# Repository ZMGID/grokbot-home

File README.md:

# grokbot-home

我的 Grok Bot「家」：换到新的 Grok Bot 账号时，让新号上的 bot 按这个仓库把自己和其他所有 bot 一起配好，做到基本无缝切换。

## 怎么用

仓库是**公开**的（2026-10-08 起），新号上的 bot 不用登录 GitHub 就能匿名克隆、读 `BOOTSTRAP.md`。Composio API key 只以**加密**形式放在 `secrets/*.enc`，解密口令只有我知道（应用连接只走 `composio-pg`，不装官方 GitHub/Origin 等连接器）。

在新号上打开任意一个 Grok Bot（一般是默认的主 bot），对它说：

```text
按这个仓库配置自己：https://github.com/ZMGID/grokbot-home
```

它会读 [`BOOTSTRAP.md`](BOOTSTRAP.md)，然后依次：

1. （Step 0）匿名克隆本仓库 → 用密码框（secret-request）向我要口令 `GROKBOT_HOME_PASSPHRASE` → 解密 `secrets/COMPOSIO_API_KEY.enc` 到 `~/.composio_pg_key`（连不上就换 `.box-current.enc`）→ 从 `connectors/composio-pg/` 装好并添加 composio-pg；
2. （Step 1）用 Composio 里 GitHub（ZMGID）的 token 登录 `gh`——只有往仓库推送（写回、每日同步）才需要；
3. 跑 `setup.sh` 装好工具环境（KiCad、PlatformIO、cadquery、Composio SDK 等）；
4. 确认 `composio-pg` 已接通；pstack 插件可选（原为 dr eggbot 安装）；导入 `skills/` 里的技能（若有）；
5. 按 `bots/grok-bot/` 设置自己为 **小萌**（主 bot；原名 Grok Bot）并读 `CONTEXT.md`；
6. 用 CreateAgent 把 `bots/` 下其他每个 bot（小枳、仓库管家、代码工程师、搭建运维、事务秘书、硬件工程师……，以 `bots/index.json` 为准）重新建出来，并重建它们的定时任务；
7. 自检，最后把新学到的东西写回仓库。

我需要亲自做的只有：在密码框里填一次仓库口令（解密失败时才要 Composio key 本身；`gh` 设备码只在推送权限拿不到时备用）。

## 目录

| 路径 | 内容 |
|---|---|
| `BOOTSTRAP.md` | 写给新 bot 的开机步骤（英文为主，附中文） |
| `CONTEXT.md` | 关于我的共享记忆：习惯、账号、项目进度、换号决定 |
| `bots/<名字>/` | 每个 bot 一个文件夹：`profile.md`（设定）、`CONTEXT.md`（它自己的记忆）、`routines.md`（定时任务） |
| `connectors/` | 连接器清单 + `composio-pg` 启动脚本（不含密钥） |
| `skills/` | 用户自建技能（目前有 `tiktok`：TikTok巴西站竞品调研） |
| `setup.sh` | 工具环境安装脚本（可重复运行） |
| `scripts/` | 每日同步任务说明和脚本、密钥扫描 `secret-scan.sh`、加解密 `secret-crypt.py` |
| `secrets/` | 只放加密后的密钥（`*.enc`），见 `secrets/README.md` |
| `projects/` | 项目文件（仿 TourBox 创作控制器） |

## 规矩

- **仓库是公开的，明文密钥永远不进仓库**。唯一例外是 `secrets/*.enc`：用 `scripts/secret-crypt.py` 加密后的 Composio key。口令只通过 bot 的密码框（secret prompt）给，绝不写进仓库或聊天。推送前必须 `bash scripts/secret-scan.sh` 通过。
- 每个号用完，新记住的东西写回对应的 `CONTEXT.md` 再推送。仓库管家每天凌晨 3:14（北京时间）自动同步一次。
- 仓库公开后，里面的共享记忆（`CONTEXT.md`、`bots/*/CONTEXT.md`、`bots/*/raw/memory/`）任何人都能看到；不要再写进不想公开的内容。不做 export-bot-template 分享模板。

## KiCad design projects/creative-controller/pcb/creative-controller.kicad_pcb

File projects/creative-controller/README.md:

# CreativeDial delivery package (Rev A1, 2026-10-08)
中文完整说明见 docs/README.md；设计审查报告（问题清单、修复、料号核验表、上电调试清单）见 **docs/审查报告.md**。

- Mechanical: mechanical/ (print-ready STL in print/)
- PCB (KiCad 9): pcb/ — regenerate with `cd pcb && ./route.sh && ./export.sh`; JLCPCB outputs in pcb/fab/
  (gerbers zip, BOM_JLCPCB.csv, CPL_JLCPCB.csv, BOM_detailed.csv with LCSC stock/price/Basic-Extended/links, ERC/DRC reports)
- Firmware: firmware/ (PlatformIO, Arduino-ESP32); prebuilt merged image firmware/bin/creativedial-esp32s3-merged.bin @0x0.
  Hardware self-test: hold TOP key while plugging in USB (or send `{"cmd":"selftest","on":true}`), watch serial at 115200.
- Config app: software/

Status: ERC 0 errors / DRC 0 errors (silkscreen warnings only), firmware builds cleanly. Not yet prototyped — see docs/审查报告.md §6 for remaining risks
(ENC2 mouse-encoder footprint is a placeholder; confirm CPL rotations in JLC preview; battery must have its own protection PCM).

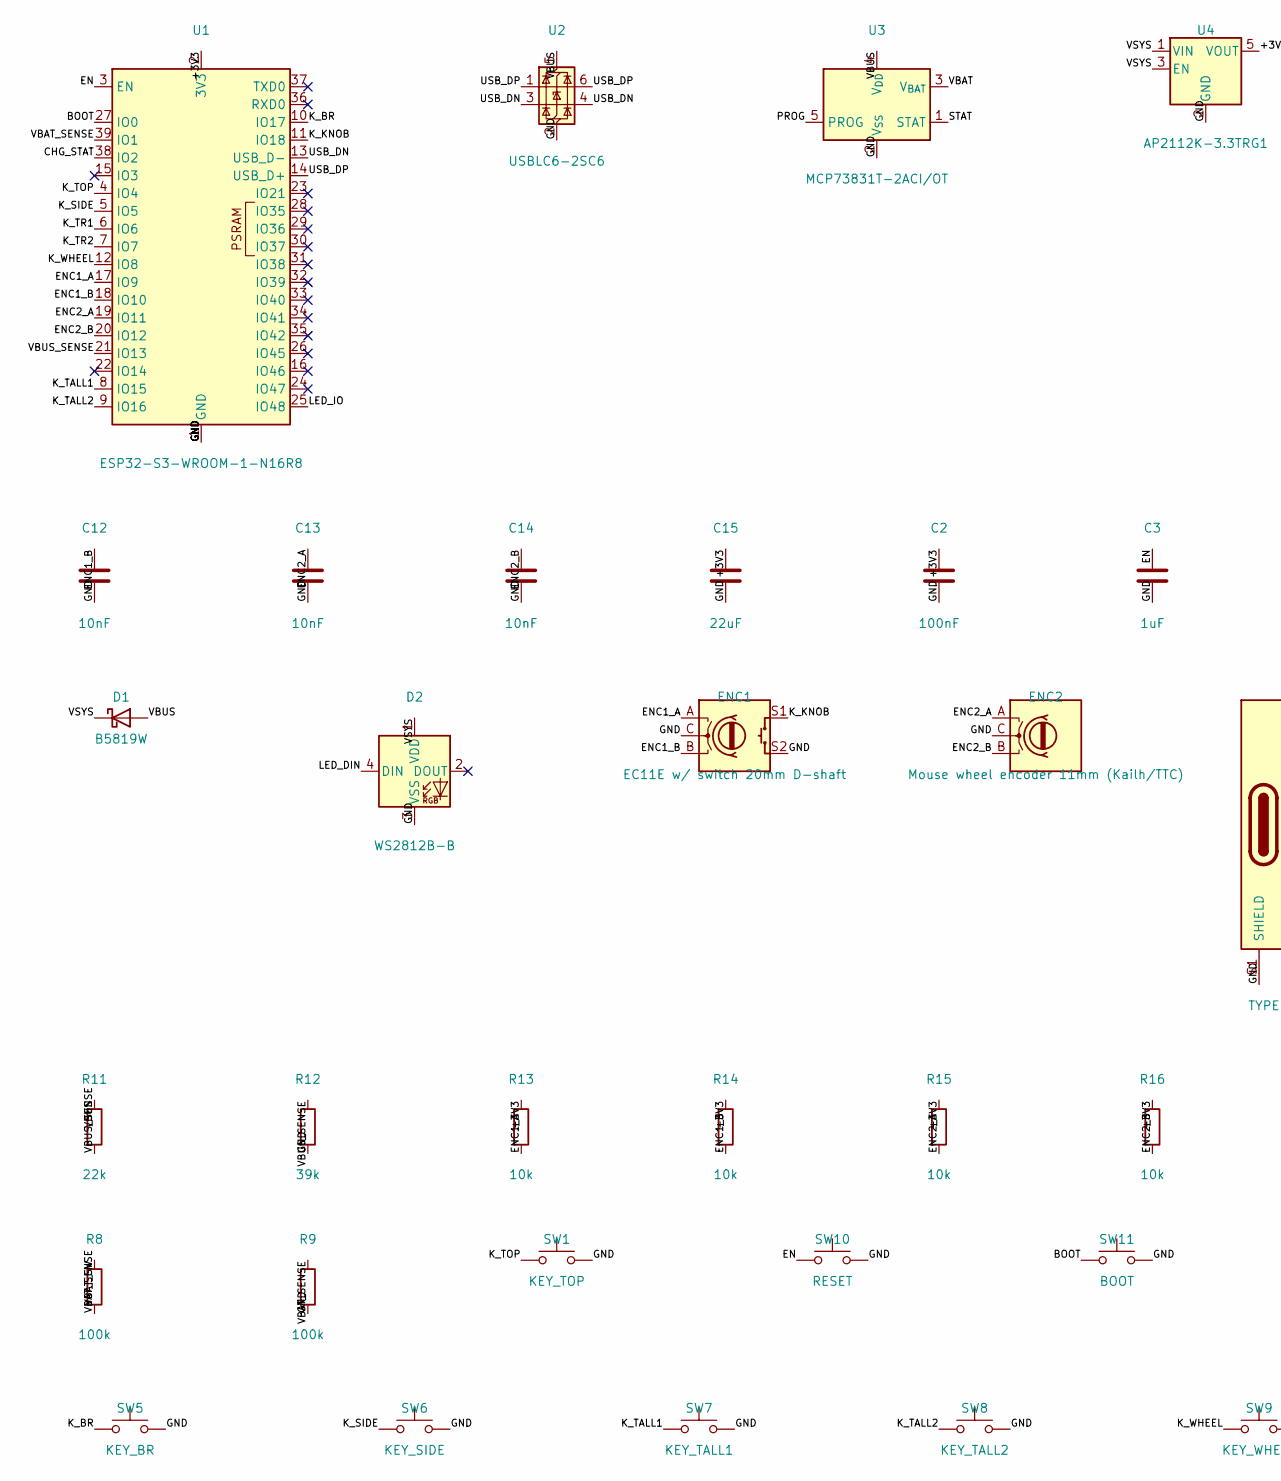
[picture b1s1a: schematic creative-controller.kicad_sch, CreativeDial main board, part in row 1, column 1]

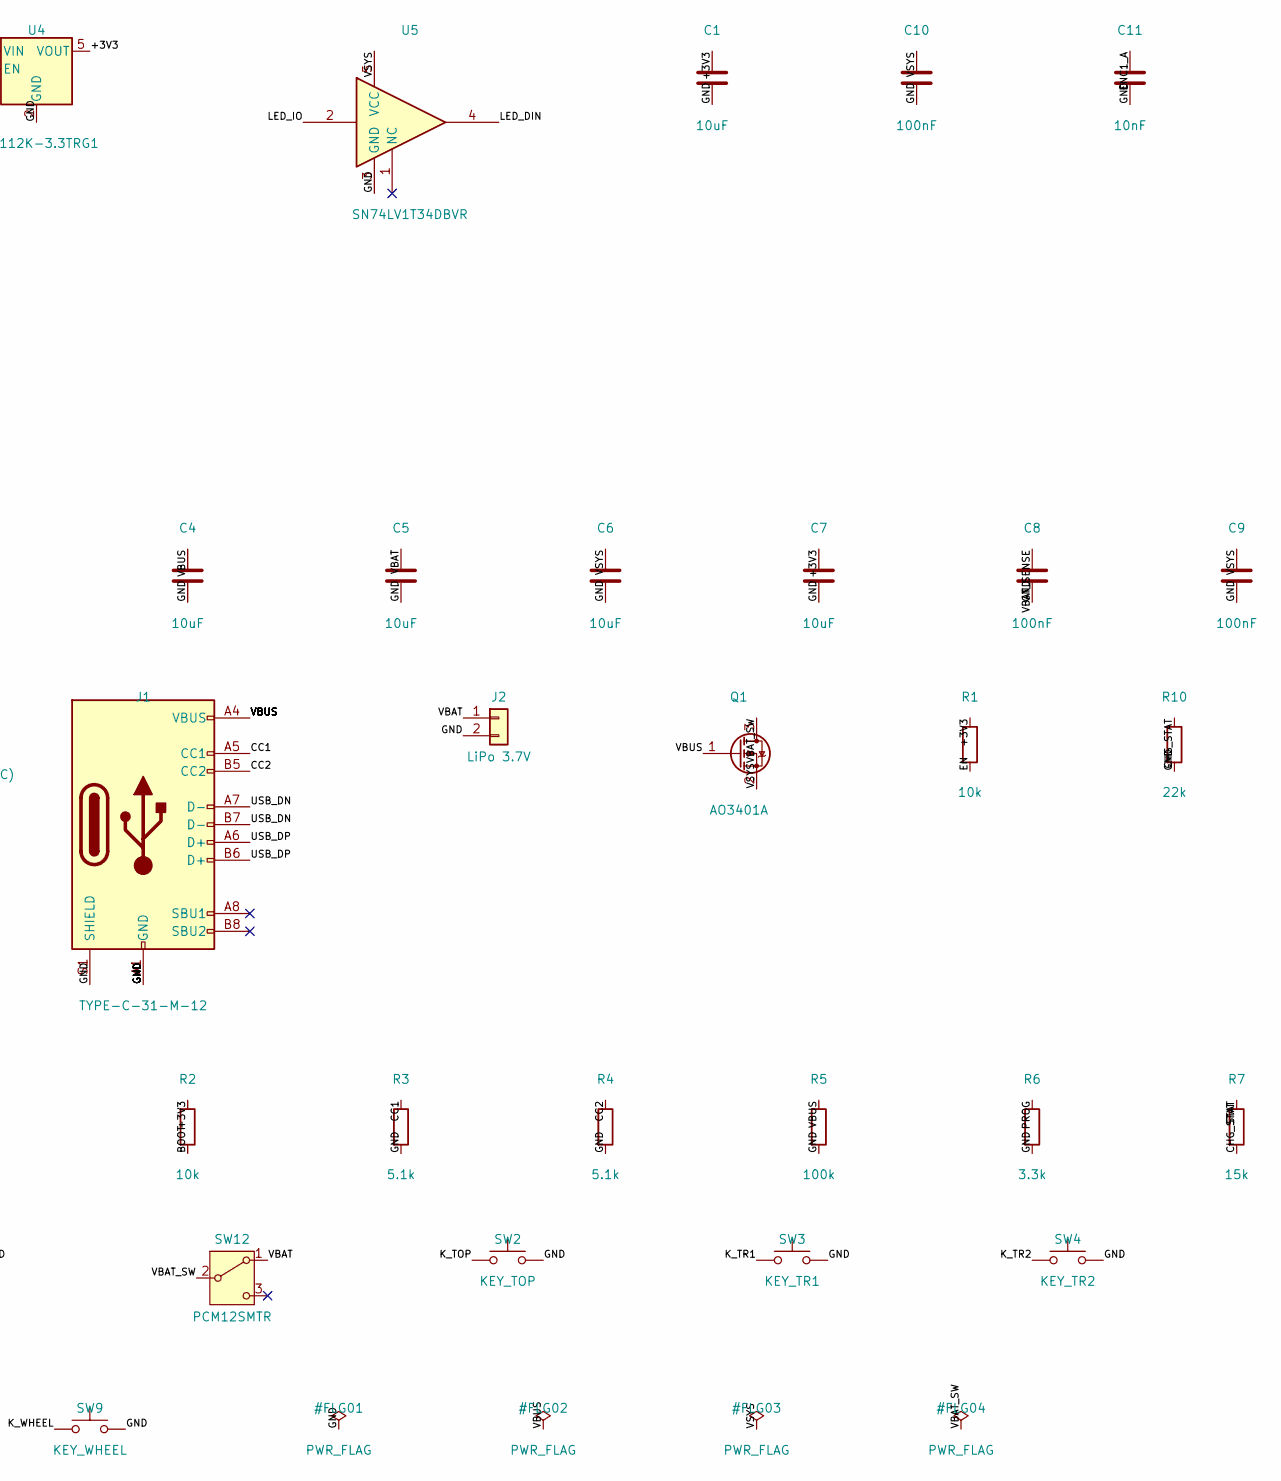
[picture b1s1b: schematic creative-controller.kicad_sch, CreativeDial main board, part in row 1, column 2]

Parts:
C1, C4, C5, C6, C7: 10uF; C_0603_1608Metric; LCSC C19702
C2, C8, C9, C10: 100nF; C_0402_1005Metric; LCSC C1525
C3: 1uF; C_0402_1005Metric; LCSC C52923
C11, C12, C13, C14: 10nF; C_0402_1005Metric; LCSC C15195
C15: 22uF; C_0805_2012Metric; LCSC C45783
D1: B5819W; D_SOD-123; LCSC C8598
D2: WS2812B-B; LED_WS2812B_PLCC4_5.0x5.0mm_P3.2mm; LCSC C2761795
ENC1: EC11E w/ switch 20mm D-shaft; RotaryEncoder_Alps_EC11E-Switch_Vertical_H20mm; LCSC C255515
ENC2: Mouse wheel encoder 11mm (Kailh/TTC); MouseEncoder_11mm_3pin
J1: TYPE-C-31-M-12; USB_C_Receptacle_HRO_TYPE-C-31-M-12; LCSC C165948
J2: LiPo 3.7V; JST_PH_S2B-PH-SM4-TB_1x02-1MP_P2.00mm_Horizontal; LCSC C295747
Q1: AO3401A; SOT-23; LCSC C15127
R1, R2, R13, R14, R15, R16: 10k; R_0402_1005Metric; LCSC C25744
R3, R4: 5.1k; R_0402_1005Metric; LCSC C25905
R5, R8, R9: 100k; R_0402_1005Metric; LCSC C25741
R6: 3.3k; R_0402_1005Metric; LCSC C25890
R7: 15k; R_0402_1005Metric; LCSC C25756
R10, R11: 22k; R_0402_1005Metric; LCSC C25768
R12: 39k; R_0402_1005Metric; LCSC C25783
SW1, SW2: KEY_TOP; SW_SPST_PTS645; LCSC C53431191
SW3: KEY_TR1; SW_SPST_PTS645; LCSC C53431191
SW4: KEY_TR2; SW_SPST_PTS645; LCSC C53431191
SW5: KEY_BR; SW_SPST_PTS645; LCSC C53431191
SW6: KEY_SIDE; SW_SPST_PTS645; LCSC C53431191
SW7: KEY_TALL1; SW_SPST_PTS645; LCSC C53431191
SW8: KEY_TALL2; SW_SPST_PTS645; LCSC C53431191
SW9: KEY_WHEEL; SW_SPST_PTS645; LCSC C53431191
SW10: RESET; SW_SPST_TL3342; LCSC C318884
SW11: BOOT; SW_SPST_TL3342; LCSC C318884
SW12: PCM12SMTR; SW_SPDT_PCM12; LCSC C221841
U1: ESP32-S3-WROOM-1-N16R8; ESP32-S3-WROOM-1; LCSC C2913202
U2: USBLC6-2SC6; SOT-23-6; LCSC C7519
U3: MCP73831T-2ACI/OT; SOT-23-5; LCSC C424093
U4: AP2112K-3.3TRG1; SOT-23-5; LCSC C51118
U5: SN74LV1T34DBVR; SOT-23-5; LCSC C100024

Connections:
/+3V3: C1.1, C2.1, C7.1, C15.1, R1.1, R2.1, R13.1, R14.1, R15.1, R16.1, U1.2 (3V3), U4.5 (VOUT)
/BOOT: R2.2, SW11.1, U1.27 (IO0)
/CC1: J1.A5 (CC1), R3.1
/CC2: J1.B5 (CC2), R4.1
/CHG_STAT: R7.2, R10.1, U1.38 (IO2)
/EN: C3.1, R1.2, SW10.1, U1.3 (EN)
/ENC1_A: C11.1, ENC1.A, R13.2, U1.17 (IO9)
/ENC1_B: C12.1, ENC1.B, R14.2, U1.18 (IO10)
/ENC2_A: C13.1, ENC2.A, R15.2, U1.19 (IO11)
/ENC2_B: C14.1, ENC2.B, R16.2, U1.20 (IO12)
/GND: C1.2, C2.2, C3.2, C4.2, C5.2, C6.2, C7.2, C8.2, C9.2, C10.2, C11.2, C12.2, C13.2, C14.2, C15.2, D2.3 (VSS), ENC1.C, ENC1.S2, ENC2.C, J1.A1 (GND), J1.A12 (GND), J1.B1 (GND), J1.B12 (GND), J1.S1 (SHIELD), J2.2, R3.2, R4.2, R5.2, R6.2, R9.2, R10.2, R12.2, SW1.2, SW2.2, SW3.2, SW4.2, SW5.2, SW6.2, SW7.2, SW8.2, SW9.2, SW10.2, SW11.2, U1.1 (GND), U1.40 (GND), U1.41 (GND), U2.2 (GND), U3.2 (V_{SS}), U4.2 (GND), U5.3 (GND)
/K_BR: SW5.1, U1.10 (IO17)
/K_KNOB: ENC1.S1, U1.11 (IO18)
/K_SIDE: SW6.1, U1.5 (IO5)
/K_TALL1: SW7.1, U1.8 (IO15)
/K_TALL2: SW8.1, U1.9 (IO16)
/K_TOP: SW1.1, SW2.1, U1.4 (IO4)
/K_TR1: SW3.1, U1.6 (IO6)
/K_TR2: SW4.1, U1.7 (IO7)
/K_WHEEL: SW9.1, U1.12 (IO8)
/LED_DIN: D2.4 (DIN), U5.4
/LED_IO: U1.25 (IO48), U5.2
/PROG: R6.1, U3.5 (PROG)
/STAT: R7.1, U3.1 (STAT)
/USB_DN: J1.A7 (D-), J1.B7 (D-), U1.13 (USB_D-), U2.3 (I/O2), U2.4 (I/O2)
/USB_DP: J1.A6 (D+), J1.B6 (D+), U1.14 (USB_D+), U2.1 (I/O1), U2.6 (I/O1)
/VBAT: C5.1, J2.1, SW12.1 (A), U3.3 (V_{BAT})
/VBAT_SENSE: C8.1, R8.2, R9.1, U1.39 (IO1)
/VBAT_SW: Q1.3 (D), R8.1, SW12.2 (B)
/VBUS: C4.1, D1.2 (A), J1.A4 (VBUS), J1.A9 (VBUS), J1.B4 (VBUS), J1.B9 (VBUS), Q1.1 (G), R5.1, R11.1, U2.5 (VBUS), U3.4 (V_{DD})
/VBUS_SENSE: R11.2, R12.1, U1.21 (IO13)
/VSYS: C6.1, C9.1, C10.1, D1.1 (K), D2.1 (VDD), Q1.2 (S), U4.1 (VIN), U4.3 (EN), U5.5 (VCC)

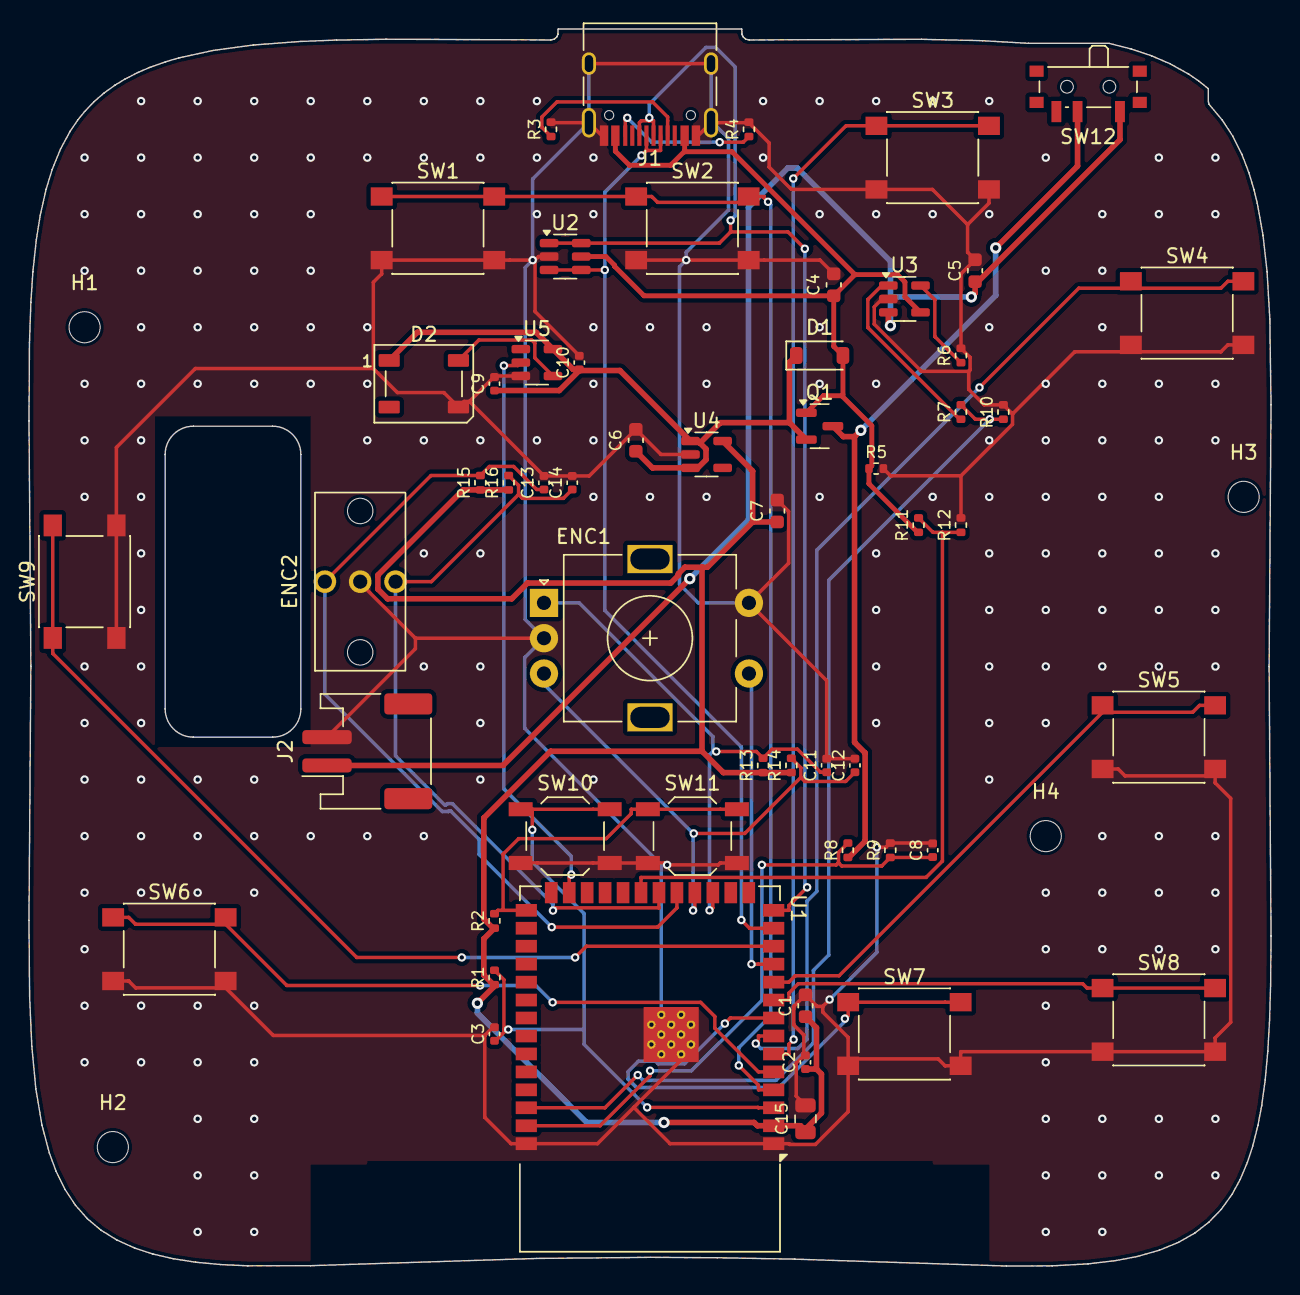
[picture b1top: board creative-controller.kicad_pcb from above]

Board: 2 copper layers, 87.9 x 87.5 mm, 59 parts (0 on the bottom side), 32 nets.

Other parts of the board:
H1, H2, H3, H4: MountingHole_2.2mm_M2

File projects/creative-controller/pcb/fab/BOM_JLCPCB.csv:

Comment,Designator,Footprint,LCSC Part #
ESP32-S3-WROOM-1-N16R8,U1,ESP32-S3-WROOM-1,C2913202
10uF,"C1,C4,C5,C6,C7",C_0603_1608Metric,C19702
100nF,"C2,C8,C10,C9",C_0402_1005Metric,C1525
22uF,C15,C_0805_2012Metric,C45783
10k,"R1,R2,R13,R14,R15,R16",R_0402_1005Metric,C25744
1uF,C3,C_0402_1005Metric,C52923
C318884 (RESET/BOOT),"SW10,SW11",SW_SPST_TL3342,C318884
TYPE-C-31-M-12,J1,USB_C_Receptacle_HRO_TYPE-C-31-M-12,C165948
5.1k,"R3,R4",R_0402_1005Metric,C25905
USBLC6-2SC6,U2,SOT-23-6,C7519
B5819W,D1,D_SOD-123,C8598
AO3401A,Q1,SOT-23,C15127
100k,"R5,R8,R9",R_0402_1005Metric,C25741
MCP73831T-2ACI/OT,U3,SOT-23-5,C424093
3.3k,R6,R_0402_1005Metric,C25890
15k,R7,R_0402_1005Metric,C25756
22k,"R10,R11",R_0402_1005Metric,C25768
39k,R12,R_0402_1005Metric,C25783
PCM12SMTR,SW12,SW_SPDT_PCM12,C221841
LiPo 3.7V,J2,JST_PH_S2B-PH-SM4-TB_1x02-1MP_P2.00mm_Horizontal,C295747
AP2112K-3.3TRG1,U4,SOT-23-5,C51118
WS2812B-B,D2,LED_WS2812B_PLCC4_5.0x5.0mm_P3.2mm,C2761795
SN74LV1T34DBVR,U5,SOT-23-5,C100024
10nF,"C11,C12,C13,C14",C_0402_1005Metric,C15195
C53431191 (KEY_TOP/KEY_TR1/KEY_TR2/KEY_BR/KEY_SIDE/KEY_TALL1/KEY_TALL2/KEY_WHEEL),"SW1,SW2,SW3,SW4,SW5,SW6,SW7,SW8,SW9",SW_SPST_PTS645,C53431191

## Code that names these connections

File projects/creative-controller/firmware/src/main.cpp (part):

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#ifndef ENC_STEPS
#define ENC_STEPS 2
#endif
#define LED_PIN 48       // GPIO48 -> U5 SN74LV1T34 (VSYS level) -> WS2812B DIN
#define VBAT_ADC 1       // GPIO1: battery (after power switch) via 100k/100k divider
#define CHG_STAT 2       // GPIO2: MCP73831 STAT via 15k/22k divider: LOW = charging (or no battery), HIGH = charge complete
#define VBUS_SENSE 13    // GPIO13: VBUS via 22k/39k divider, HIGH = USB power present

USBHIDKeyboard Keyboard;
USBHIDConsumerControl Consumer;
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void setup() {
  for (int k = 0; k < NKEYS; k++) { if (rtc_gpio_is_valid_gpio((gpio_num_t)KEY_PINS[k])) rtc_gpio_deinit((gpio_num_t)KEY_PINS[k]);
    pinMode(KEY_PINS[k], INPUT_PULLUP); }
  pinMode(CHG_STAT, INPUT);            // external 15k/22k divider, no pull
  pinMode(VBUS_SENSE, INPUT);          // external 22k/39k divider
  analogSetPinAttenuation(VBAT_ADC, ADC_11db);
  for (auto &e : encs) { pinMode(e.a, INPUT_PULLUP); pinMode(e.b, INPUT_PULLUP);
    e.st = (digitalRead(e.a) << 1) | digitalRead(e.b);
    attachInterruptArg(e.a, encIsr, &e, CHANGE); attachInterruptArg(e.b, encIsr, &e, CHANGE); }
  loadCfg();
  { int ws = cfg["wheel_steps"] | ENC_STEPS; encs[1].steps = (ws == 4) ? 4 : 2; int ks_ = cfg["knob_steps"] | ENC_STEPS; encs[0].steps = (ks_ == 4) ? 4 : 2; }
  delay(20); selftest = !digitalRead(KEY_PINS[K_TOP]);   // hold TOP key while powering on -> self-test mode
  Keyboard.begin(); Consumer.begin();
  USB.productName("CreativeDial"); USB.manufacturerName("OpenMaker"); USB.begin();
  Serial.begin(115200);
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    bool usb = usbPower(), chg = charging(); int mv = batteryMv();
    // LED: orange = charging, green = charged, blue = BLE connected, dim cyan = USB HID only, off on low battery
    if (chg) neopixelWrite(LED_PIN, 30, 8, 0);
    else if (usb && digitalRead(CHG_STAT)) neopixelWrite(LED_PIN, 0, 25, 0);
    else if (mv < 3450 && !usb) neopixelWrite(LED_PIN, 0, 0, 0);
    else if (bleConn) neopixelWrite(LED_PIN, 0, 0, 25);
    else neopixelWrite(LED_PIN, 0, usbMounted() ? 8 : 0, usbMounted() ? 8 : 4);
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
